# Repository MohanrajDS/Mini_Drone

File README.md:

# Micro Drone Flight Controller

A compact 4-layer flight-controller PCB for micro drones, built around a **Seeed XIAO ESP32-S3** module, an **MPU-6050** IMU and four low-side MOSFET motor drivers for brushed (coreless) DC motors. The board measures about **17.75 x 20.95 mm** and is designed in KiCad 9.

## Features

- ESP32-S3 (XIAO form factor) mounted on the board, with USB-C for programming
- MPU-6050 6-axis IMU on I2C
- 4 independent motor channels: AO3400A N-MOSFET low-side switch plus a 1N4148WT flyback diode per motor
- 2-pin JST-EH battery connector feeding the motor supply rail
- Test pads on every motor terminal, the battery rail and ground
- 4-layer stack-up: F.Cu / In1.Cu (power) / In2.Cu / B.Cu
- Fully custom symbol and footprint library (`Drone_prj`) and a 3D model for the XIAO module

## Hardware overview

| Item | Detail |
|---|---|
| MCU | Seeed XIAO ESP32-S3 (U1) |
| IMU | InvenSense MPU-6050, QFN-24 4x4 mm (U2), I2C address `0x68` (AD0 tied to GND) |
| Motor drivers | 4x AO3400A (Q1-Q4), SOT-23, low-side, with 1N4148WT flyback diodes (D1, D2, D3, D5) |
| Battery input | JST-EH 2-pin (J1) |
| Board size | about 17.75 x 20.95 mm |
| Layers | 4 |
| Tool | KiCad 9.0 |

### Pin map

| XIAO pin | Function |
|---|---|
| D0 | Motor 1 gate (Q1) |
| D10 | Motor 2 gate (Q2) |
| D3 | Motor 3 gate (Q3) |
| D8 | Motor 4 gate (Q4) |
| D4 | I2C SDA (MPU-6050) |
| D5 | I2C SCL (MPU-6050) |
| D1, D2 | Routed to the edge pads, not used by on-board circuitry |
| D6, D7, D9 | Not connected on the board |

The MPU-6050 interrupt pin is not connected to the MCU, so the IMU has to be polled.

### Motor connections

Each motor connects between a battery-rail pad and its switched drain pad:

| Motor | MOSFET | Switched pad |
|---|---|---|
| 1 | Q1 | TP5 |
| 2 | Q2 | TP6 |
| 3 | Q3 | TP7 |
| 4 | Q4 | TP8 |

Battery-rail pads are TP1-TP4 (and TP9); TP10 is ground.

### Power

The battery connector (J1) feeds the `BAT+` rail, which supplies the motors through the MOSFETs. The logic rail (`+3V3`) is taken from the XIAO module's 3V3 pin and supplies the MPU-6050.

## Schematic

The full schematic is also available as a [PDF](docs/Mini_Drone_schematic.pdf).

## Repository layout

```
hardware/         KiCad project: schematic, PCB, symbol/footprint library, 3D model
docs/             Schematic PDF and images used in this README
manufacturing/    Gerber + drill files (zip) and bill of materials
```

## Open the design

1. Install [KiCad](https://www.kicad.org/) 9 or newer.
2. Open `hardware/Mini_Drone.kicad_pro`.

The project-local library (`Drone_prj`) and the 3D model are referenced relative to the project folder, so no extra setup is needed.

## Manufacturing

`manufacturing/Mini_Drone_gerbers.zip` contains Gerber files for all four copper layers, solder mask, paste, silkscreen and board outline, plus the Excellon drill file. The bill of materials is in `manufacturing/Mini_Drone_bom.csv`.

## Design checks

Run with the KiCad 10 command-line tools on the files in `hardware/`:

- **ERC:** 0 errors, 2 warnings (one single-pin label, one unconnected wire end)
- **DRC:** no clearance, short or unconnected-item errors. The 12 reported errors are courtyard overlaps between other components and the XIAO module (U1) footprint area, a result of the compact layout. The remaining warnings are silkscreen overlaps/clipping and library-footprint overrides.

## Firmware

Firmware is not part of this repository yet.

## Author

Mohanraj D S - [github.com/MohanrajDS](https://github.com/MohanrajDS)

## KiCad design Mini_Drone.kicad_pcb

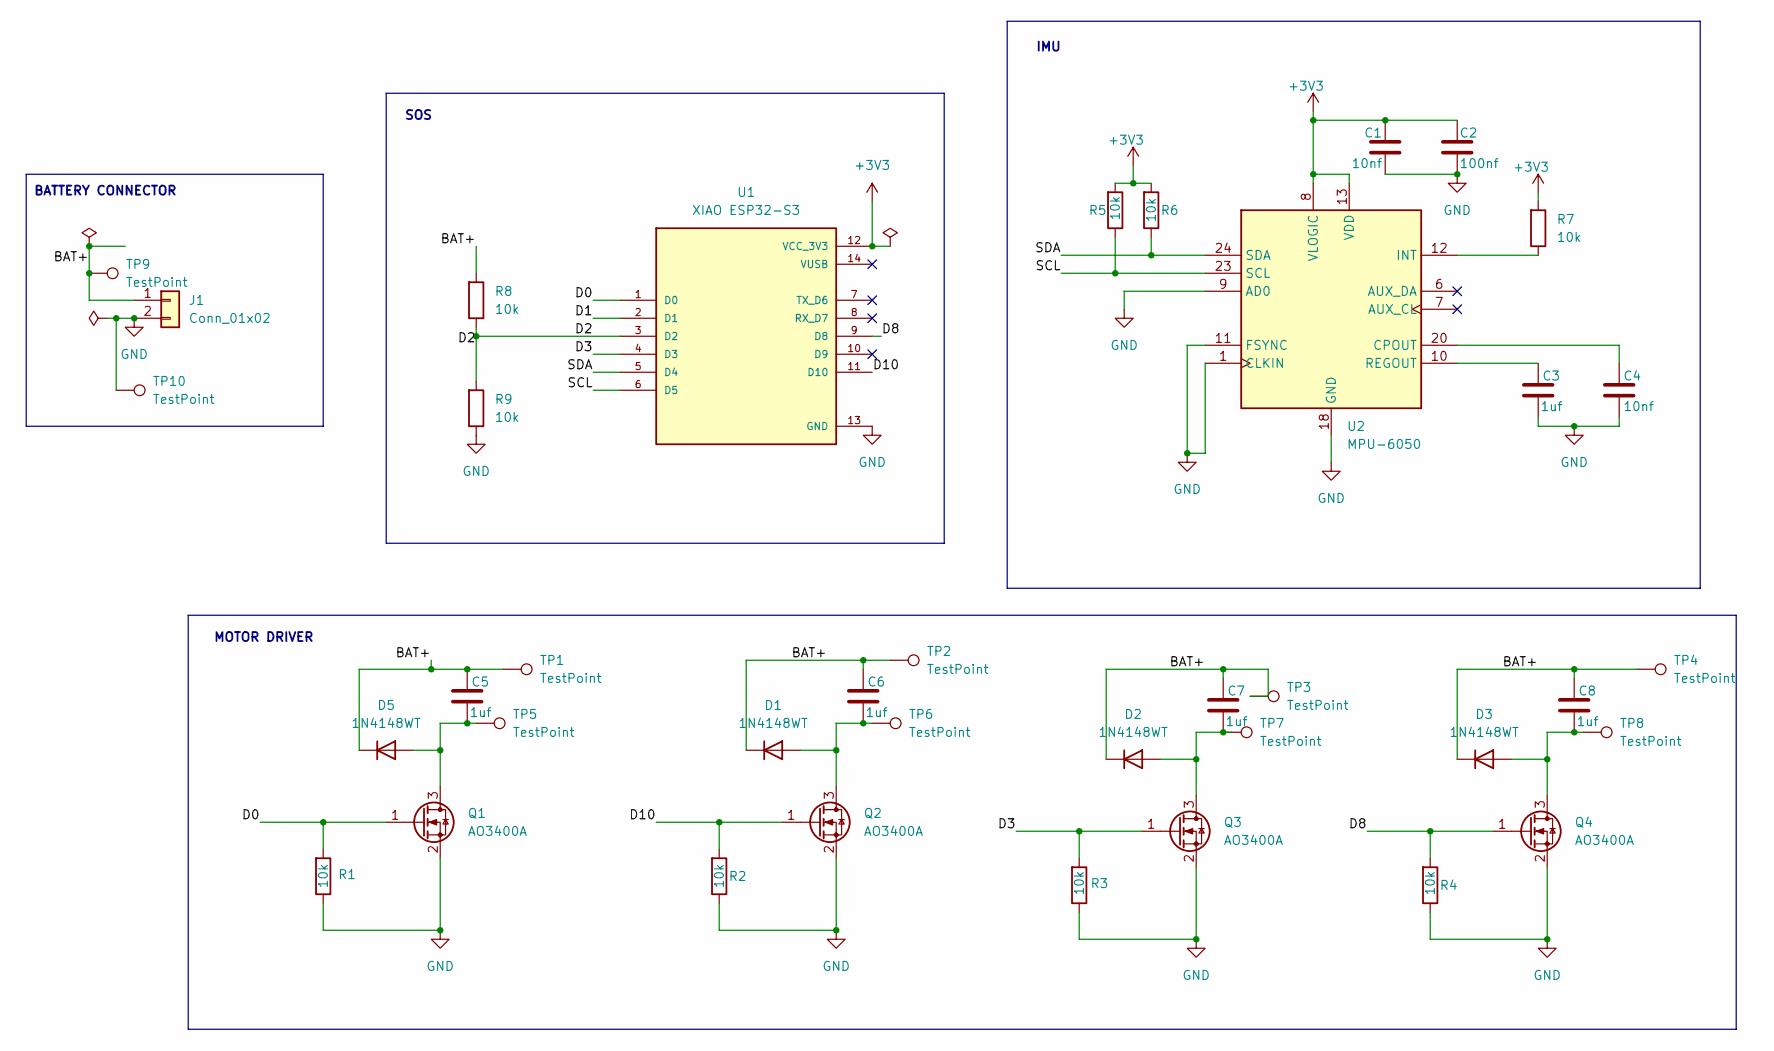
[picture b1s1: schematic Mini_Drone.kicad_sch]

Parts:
C1, C4: 10nf; C_0603_1608Metric
C2: 100nf; C_0603_1608Metric
C3, C5, C6, C7, C8: 1uf; C_0603_1608Metric
D1, D2, D3, D5: 1N4148WT; D_SOD-523
J1: Conn_01x02; JST_EH_S2B-EH_1x02_P2.50mm_Horizontal
Q1, Q2, Q3, Q4: AO3400A; SOT-23
R1, R2, R3, R4, R5, R6, R7, R8, R9: 10k; R_0603_1608Metric; MFR.Part # 0603WAF1002T5E; LCSC Part # C25804
TP1, TP2, TP3, TP4, TP5, TP6, TP7, TP8: TestPoint; TestPoint_Pad_D1.0mm
TP9, TP10: TestPoint; TestPoint_Pad_1.5x1.5mm
U1: XIAO ESP32-S3; PARTREV 23/05/2022
U2: MPU-6050; InvenSense_QFN-24_4x4mm_P0.5mm

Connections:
+3V3: C1.1, C2.1, R5.1, R6.1, R7.1, U1.12 (VCC_3V3), U2.8 (VLOGIC), U2.13 (VDD)
/BAT+: C5.1, C6.1, C7.1, C8.1, D1.1 (K), D2.1 (K), D3.1 (K), D5.1 (K), J1.1, R8.1, TP1.1, TP2.1, TP3.1, TP4.1, TP9.1
/D0: Q1.1 (G), R1.1, U1.1 (D0)
/D1: U1.2 (D1)
/D2: R8.2, R9.1, U1.3 (D2)
/D3: Q3.1 (G), R3.1, U1.4 (D3)
/D8: Q4.1 (G), R4.1, U1.9 (D8)
/D10: Q2.1 (G), R2.1, U1.11 (D10)
/SCL: R5.2, U1.6 (D5), U2.23 (SCL)
/SDA: R6.2, U1.5 (D4), U2.24 (SDA)
GND: C1.2, C2.2, C3.2, C4.2, J1.2, Q1.2 (S), Q2.2 (S), Q3.2 (S), Q4.2 (S), R1.2, R2.2, R3.2, R4.2, R9.2, TP10.1, U1.13 (GND), U2.1 (CLKIN), U2.9 (AD0), U2.11 (FSYNC), U2.18 (GND)
unnamed: C6.2, D1.2 (A), Q2.3 (D), TP6.1
unnamed: C7.2, D2.2 (A), Q3.3 (D), TP7.1
unnamed: C8.2, D3.2 (A), Q4.3 (D), TP8.1
unnamed: C5.2, D5.2 (A), Q1.3 (D), TP5.1
unnamed: C4.1, U2.20 (CPOUT)
unnamed: R7.2, U2.12 (INT)
unnamed: C3.1, U2.10 (REGOUT)

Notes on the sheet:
SOS
BATTERY CONNECTOR
IMU
MOTOR DRIVER

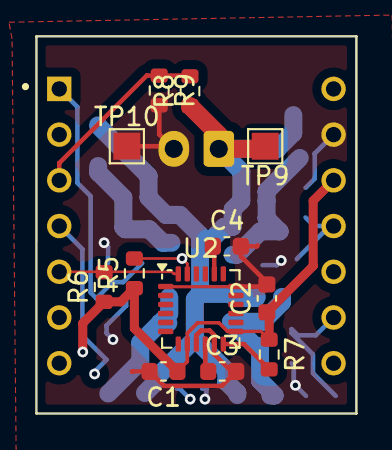
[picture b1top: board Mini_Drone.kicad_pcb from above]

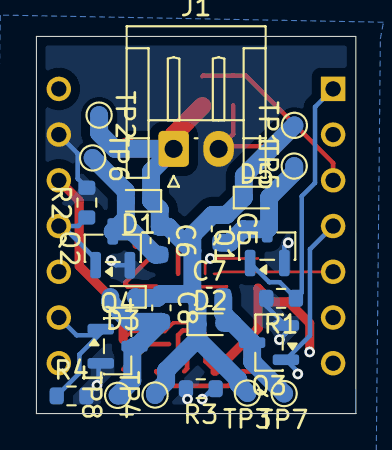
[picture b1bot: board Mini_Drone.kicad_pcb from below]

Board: 4 copper layers, 17.8 x 21.0 mm, 38 parts (25 on the bottom side), 17 nets.

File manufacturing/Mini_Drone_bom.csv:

"Reference","Value","Footprint","Qty"
"C1,C4","10nf","Capacitor_SMD:C_0603_1608Metric","2"
"C2","100nf","Capacitor_SMD:C_0603_1608Metric","1"
"C3,C5-C8","1uf","Capacitor_SMD:C_0603_1608Metric","5"
"D1-D3,D5","1N4148WT","Diode_SMD:D_SOD-523","4"
"J1","Conn_01x02","Connector_JST:JST_EH_S2B-EH_1x02_P2.50mm_Horizontal","1"
"Q1-Q4","AO3400A","Package_TO_SOT_SMD:SOT-23","4"
"R1-R9","10k","Resistor_SMD:R_0603_1608Metric","9"
"TP1-TP8","TestPoint","TestPoint:TestPoint_Pad_D1.0mm","8"
"TP9,TP10","TestPoint","TestPoint:TestPoint_Pad_1.5x1.5mm","2"
"U1","XIAO ESP32-S3","Drone_prj:XIAO ESP32-S3","1"
"U2","MPU-6050","Drone_prj:InvenSense_QFN-24_4x4mm_P0.5mm","1"

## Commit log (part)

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2025-10-14 Initial Stage empty
2025-10-16 Motor Drivers no cap
2025-10-17 Version 1
2025-10-17 espfly ver1
2025-10-18 drc for sch checked
2025-10-18 trace thick updted
2025-10-18 few changes
2025-10-19 1 unconnected
2025-10-19 good progress
2025-10-19 no errors success
2025-10-19 sch organized no error success
2025-12-20 drc has been checked simulation can be done by migrating this to altium designer
2025-12-20 Initialize README with project details
    Added detailed project description, features, and hardware highlights for the Micro Drone Flight Controller.
